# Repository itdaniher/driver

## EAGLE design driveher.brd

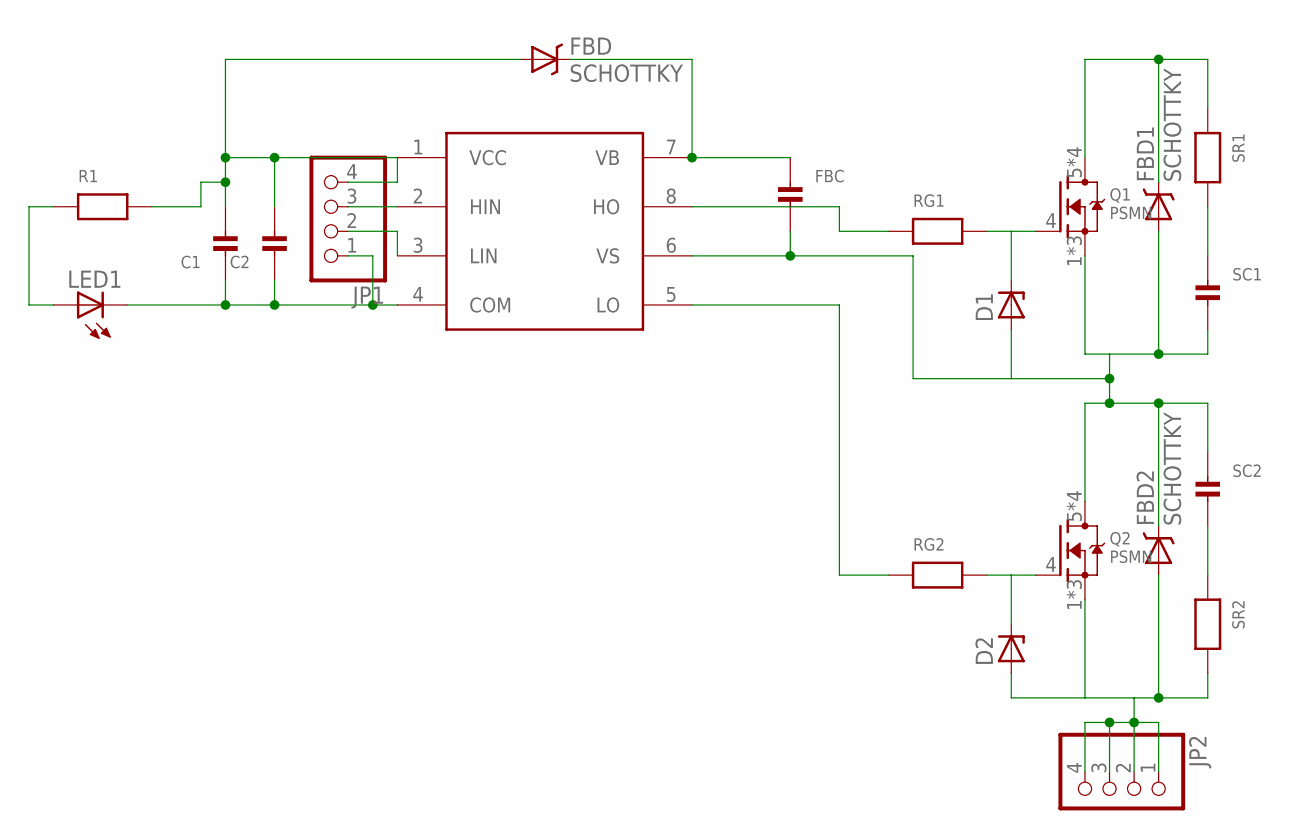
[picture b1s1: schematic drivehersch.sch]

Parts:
C1, C2: CAP_CERAMIC1206; 1206
D1, D2: ZENER-DIODESOT23; SOT23
FBC: CAP_CERAMIC1206; 1206
FBD, FBD1, FBD2: SCHOTTKY; SMA-DIODE
JP1, JP2: HEADER-1X4ROUND; 1X04_ROUND
LED1: LEDCHIPLED_0603; CHIPLED_0603
Q1, Q2: PSMN; SO-08
R1: RESISTOR0603; 0603
RG1, RG2: RESISTOR0603; 0603
SC1, SC2: CAP_CERAMIC0603; 0603
SR1, SR2: RESISTOR0603; 0603
U$1: IRS218-67; SO-08

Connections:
12V: C1.2, C2.2, FBD.A, JP1.4, R1.2, U$1.1 (VCC)
FLOAT: FBC.1, FBD.C, U$1.7 (VB)
G1: D1.3 (C), Q1.4 (G), RG1.2
G2: D2.3 (C), Q2.4 (G), RG2.2
GND: C1.1, C2.1, D2.1 (A), FBD2.A, JP1.1, JP2.1, JP2.2, JP2.3, JP2.4, LED1.C, Q2.1 (S), Q2.2 (S), Q2.3 (S), SR2.2, U$1.4 (COM)
HIN: JP1.3, U$1.2 (HIN)
HOUT: RG1.1, U$1.8 (HO)
LIN: JP1.2, U$1.3 (LIN)
LOUT: RG2.1, U$1.5 (LO)
unnamed: LED1.A, R1.1
unnamed: SC1.1, SR1.2
OUT: D1.1 (A), FBC.2, FBD1.A, FBD2.C, Q1.1 (S), Q1.2 (S), Q1.3 (S), Q2.5 (D), Q2.6 (D), Q2.7 (D), Q2.8 (D), SC1.2, SC2.1, U$1.6 (VS)
P2: SC2.2, SR2.1
V+: FBD1.C, Q1.5 (D), Q1.6 (D), Q1.7 (D), Q1.8 (D), SR1.1

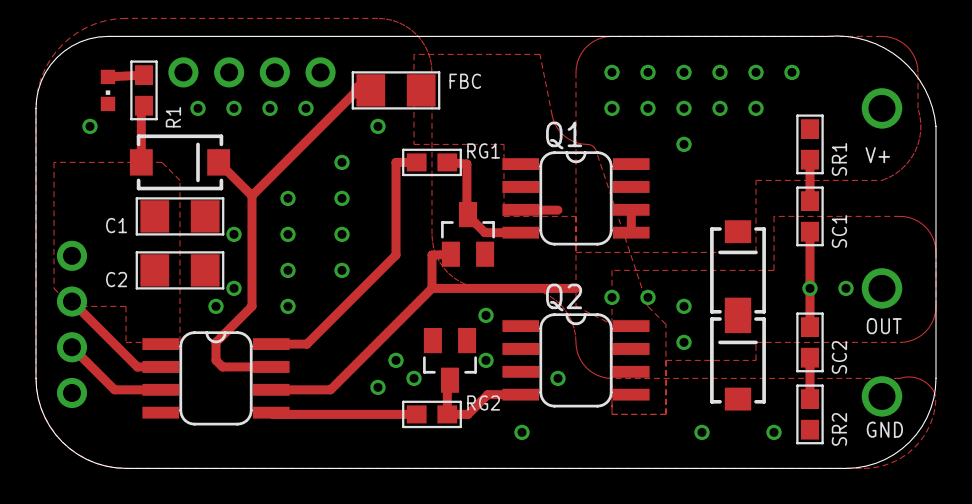
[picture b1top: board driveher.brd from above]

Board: 2 copper layers, 50.0 x 24.0 mm, 21 parts (0 on the bottom side), 14 nets.

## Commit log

2013-04-25 initial commit of 1kw in 2" drive board
2013-04-25 those do not belong there!
2013-05-30 fixed ir25606 / '67 routing, beefed up trace b/t high side source & output, added input protect resistors
2014-10-25 additional design docs
